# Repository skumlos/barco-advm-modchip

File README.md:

Arduino Mini Pro clone with Atmega328PB, Barco Edition

This is basically an Arduino Mini Pro clone but with an Atmega328PB instead of Atmega328P.
The generic components that are needed when modding Barco ADVM monitors have been added
to make the mod "prettier".

Speed 16MHz and 5V.

The reasoning is to have the secondary I2C controller of the PB version, thus PE0 and PE1
pins are pulled to 2.54mm THT holes just like A4/A5 pins of the primary I2C controller.
These are then connected to the buffer already so no extra breakout PCB and intermediate
resistors are needed.

It is still recommended to add a 100R resistor to SDA and SCL lines right at the pads of
the original resistors on the signal PCB.

Remember to burn a bootloader and fuses with a *real* programmer (like another Arduino
turned into an ISP). This requires you to connect to the ICSP pins, MOSI, MISO, SCK,
RESET, 5V and GND. I used a male pin header row  which I didn't solder but just held in
place during programming.

(2024) Martin Hejnfelt, martin@hejnfelt.com

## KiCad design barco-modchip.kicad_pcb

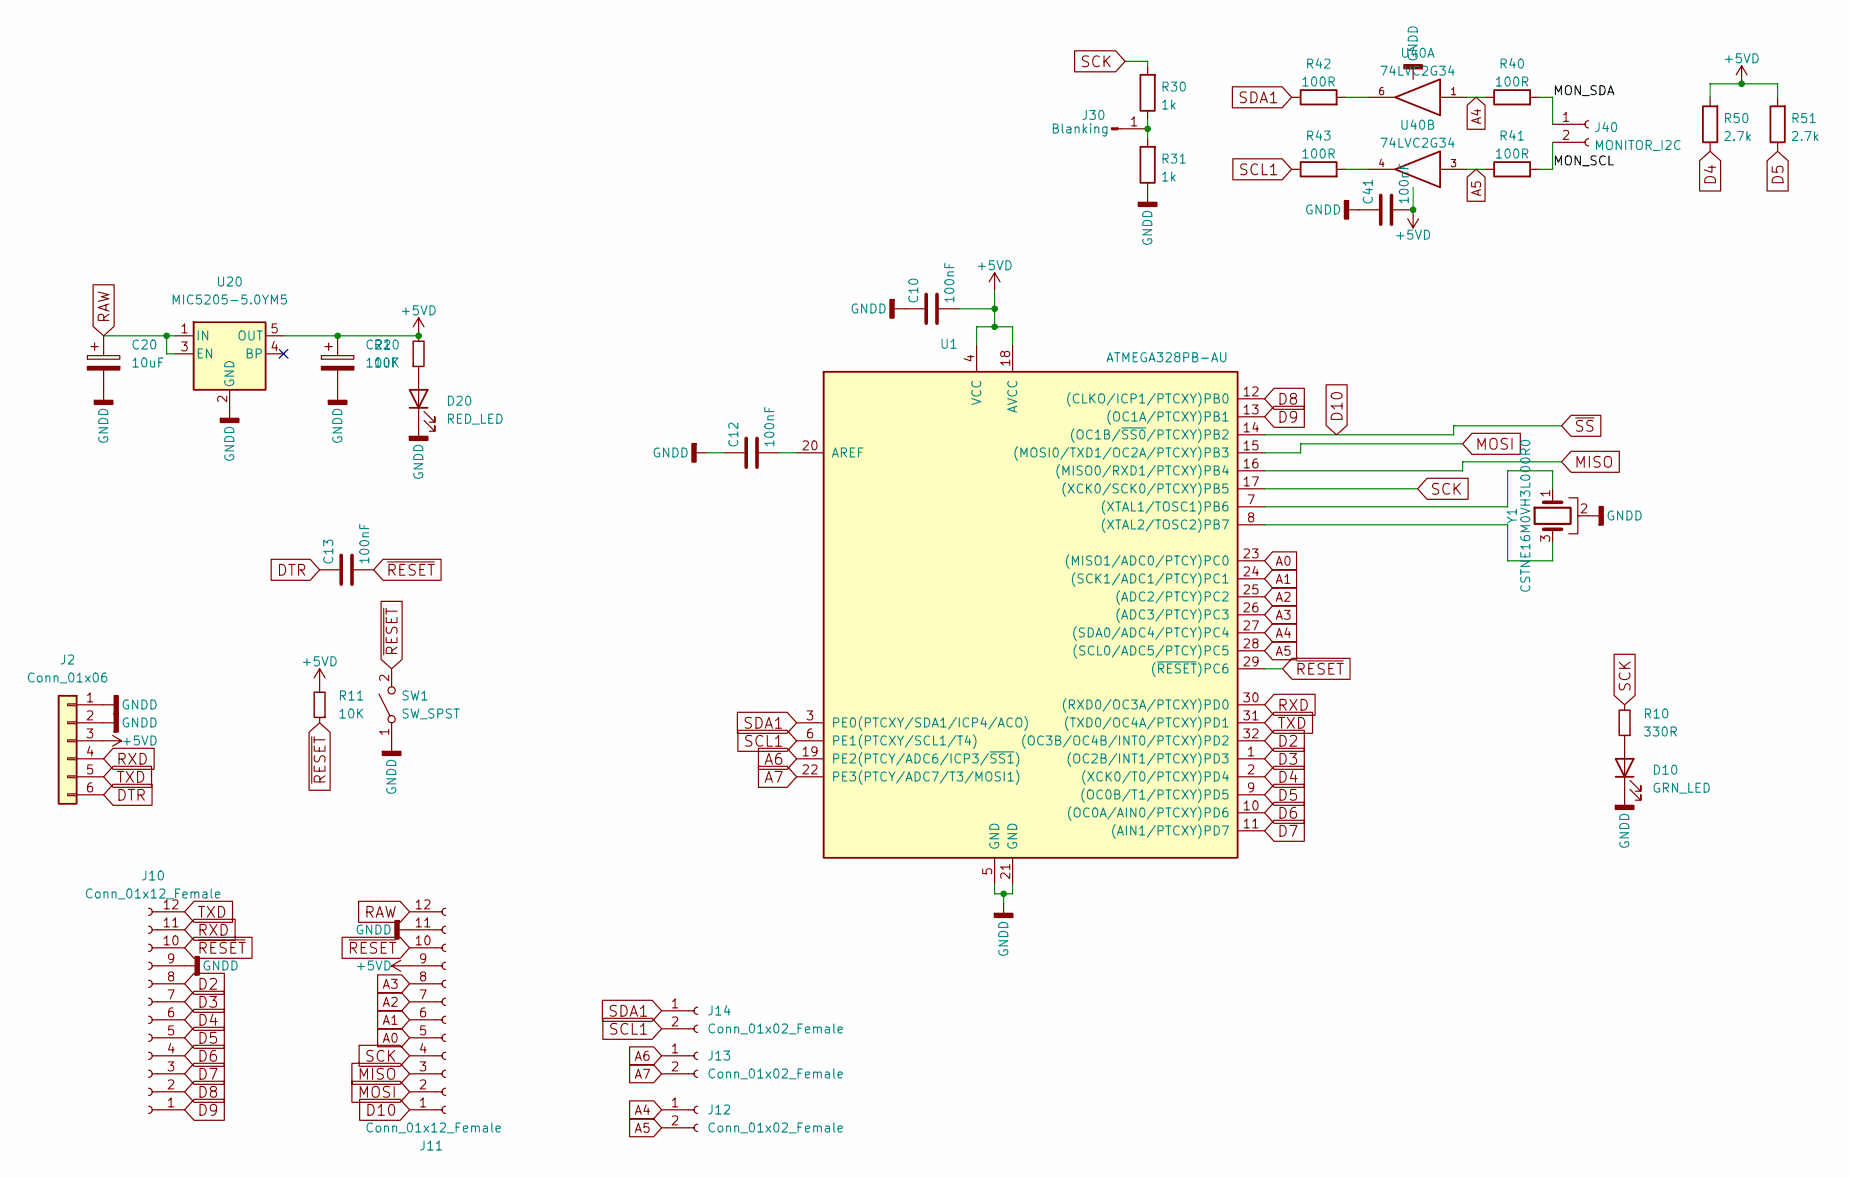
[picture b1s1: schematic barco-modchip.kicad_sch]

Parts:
C10, C12, C13, C41: 100nF; C_0603_1608Metric
C20, C21: 10uF; CP_EIA-3216-18_Kemet-A
D10: GRN_LED; LED_0603_1608Metric
D20: RED_LED; LED_0603_1608Metric
J2: Conn_01x06; PinHeader_1x06_P2.54mm_Horizontal
J10, J11: Conn_01x12_Female; PinHeader_1x12_P2.54mm_Vertical
J12, J13, J14: Conn_01x02_Female; PinHeader_1x02_P2.54mm_Vertical
J30: Blanking; TestPoint_THTPad_D2.0mm_Drill1.0mm
J40: MONITOR_I2C; PinHeader_1x02_P2.54mm_Vertical
R10: 330R; R_0603_1608Metric
R11, R20: 10K; R_0603_1608Metric
R30, R31: 1k; R_0603_1608Metric
R40, R41, R42, R43: 100R; R_0603_1608Metric
R50, R51: 2.7k; R_0603_1608Metric
SW1: SW_SPST; SW_Tactile_SPST_NO_Straight_CK_PTS636Sx25SMTRLFS
U1: ATMEGA328PB-AU; TQFP-32_7x7mm_P0.8mm
U20: MIC5205-5.0YM5; SOT-23-5
U40: 74LVC2G34; SOT-23-6
Y1: CSTNE16M0VH3L000R0; Resonator_SMD_Murata_CSTxExxV-3Pin_3.0x1.1mm

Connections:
+5VD: C10.2, C21.1, C41.2, J2.3, J11.9, R11.2, R20.2, R50.2, R51.2, U1.4 (VCC), U1.18 (AVCC), U20.5 (OUT), U40.5 (VCC)
/MON_SCL: J40.2, R41.2
/MON_SDA: J40.1, R40.2
A0: J11.5, U1.23 ((MISO1/ADC0/PTCY)PC0)
A1: J11.6, U1.24 ((SCK1/ADC1/PTCY)PC1)
A2: J11.7, U1.25 ((ADC2/PTCY)PC2)
A3: J11.8, U1.26 ((ADC3/PTCY)PC3)
A4: J12.1, R40.1, U1.27 ((SDA0/ADC4/PTCY)PC4), U40.1
A5: J12.2, R41.1, U1.28 ((SCL0/ADC5/PTCY)PC5), U40.3
A6: J13.1, U1.19 (PE2(PTCY/ADC6/ICP3/~SS1))
A7: J13.2, U1.22 (PE3(PTCY/ADC7/T3/MOSI1))
D2: J10.8, U1.32 ((OC3B/OC4B/INT0/PTCXY)PD2)
D3: J10.7, U1.1 ((OC2B/INT1/PTCXY)PD3)
D4: J10.6, R50.1, U1.2 ((XCK0/T0/PTCXY)PD4)
D5: J10.5, R51.1, U1.9 ((OC0B/T1/PTCXY)PD5)
D6: J10.4, U1.10 ((OC0A/AIN0/PTCXY)PD6)
D7: J10.3, U1.11 ((AIN1/PTCXY)PD7)
D8: J10.2, U1.12 ((CLKO/ICP1/PTCXY)PB0)
D9: J10.1, U1.13 ((OC1A/PTCXY)PB1)
D10: J11.1, U1.14 ((OC1B/~SS0/PTCXY)PB2)
DTR: C13.1, J2.6
GND: C10.1, C12.1, C20.2, C21.2, C41.1, D10.1 (K), D20.1 (K), J2.1, J2.2, J10.9, J11.11, R31.1, SW1.1 (A), U1.5 (GND), U1.21 (GND), U20.2 (GND), U40.2 (GND), Y1.2
MISO: J11.3, U1.16 ((MISO0/RXD1/PTCXY)PB4)
MOSI: J11.2, U1.15 ((MOSI0/TXD1/OC2A/PTCXY)PB3)
unnamed: C12.2, U1.20 (AREF)
unnamed: D10.2 (A), R10.1
unnamed: D20.2 (A), R20.1
unnamed: J30.1, R30.1, R31.2
unnamed: R42.2, U40.6
unnamed: R43.2, U40.4
unnamed: U1.7 ((XTAL1/TOSC1)PB6), Y1.1
unnamed: U1.8 ((XTAL2/TOSC2)PB7), Y1.3
RAW: C20.1, J11.12, U20.1 (IN), U20.3 (EN)
RXD: J2.4, J10.11, U1.30 ((RXD0/OC3A/PTCXY)PD0)
SCK: J11.4, R10.2, R30.2, U1.17 ((XCK0/SCK0/PTCXY)PB5)
SCL1: J14.2, R43.1, U1.6 (PE1(PTCXY/SCL1/T4))
SDA1: J14.1, R42.1, U1.3 (PE0(PTCXY/SDA1/ICP4/ACO))
TXD: J2.5, J10.12, U1.31 ((TXD0/OC4A/PTCXY)PD1)
~RESET: C13.2, J10.10, J11.10, R11.1, SW1.2 (B), U1.29 ((~RESET)PC6)

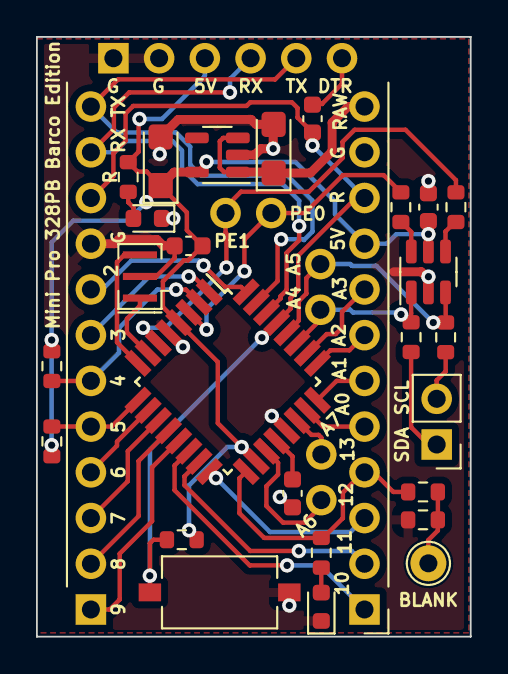
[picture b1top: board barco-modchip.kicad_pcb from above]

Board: 2 copper layers, 24.1 x 33.3 mm, 32 parts (0 on the bottom side), 39 nets.

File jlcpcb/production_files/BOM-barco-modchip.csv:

Comment,Designator,Footprint,LCSC
100R,"R40,R41,R42,R43",R_0603_1608Metric,C105588
330R,R10,R_0603_1608Metric,C105881
2.7k,"R50,R51",R_0603_1608Metric,C114612
ATMEGA328PB-AU,U1,TQFP-32_7x7mm_P0.8mm,C132230
100nF,"C10,C12,C13,C41",C_0603_1608Metric,C14663
1k,"R30,R31",R_0603_1608Metric,C22548
RED_LED,D20,LED_0603_1608Metric,C2286
10K,"R11,R20",R_0603_1608Metric,C25804
SW_SPST,SW1,SW_Tactile_SPST_NO_Straight_CK_PTS636Sx25SMTRLFS,C2689642
74LVC2G34,U40,SOT-23-6,C347589
MIC5205-5.0YM5,U20,SOT-23-5,C70431
10uF,"C20,C21",CP_EIA-3216-18_Kemet-A,C7171
GRN_LED,D10,LED_0603_1608Metric,C72038
CSTNE16M0VH3L000R0,Y1,Resonator_SMD_Murata_CSTxExxV-3Pin_3.0x1.1mm,C882605
Conn_01x12_Female,J11,PinHeader_1x12_P2.54mm_Vertical,
Conn_01x06,J2,PinHeader_1x06_P2.54mm_Horizontal,
Conn_01x12_Female,J10,PinHeader_1x12_P2.54mm_Vertical,
Conn_01x02_Female,J12,PinHeader_1x02_P2.54mm_Vertical,
Conn_01x02_Female,J14,PinHeader_1x02_P2.54mm_Vertical,
Conn_01x02_Female,J13,PinHeader_1x02_P2.54mm_Vertical,
Blanking,J30,TestPoint_THTPad_D2.0mm_Drill1.0mm,
MONITOR_I2C,J40,PinHeader_1x02_P2.54mm_Vertical,
